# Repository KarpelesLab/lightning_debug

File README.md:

# Lightning debug board

A carrier board for an eLabGuy Lightning **male** breakout, for poking at (early)
iPhones from Linux. Plug a phone into the breakout and you get:

- **An FPGA on every Lightning signal pin.** All 12 data/ID contacts (both sides
  of the plug) go to an iCE40UP5K. It can sniff, emulate an accessory/cable chip
  (ID0/ID1), or drive a UART on the data lanes and stream it to the host.
- **USB-C #1 (DEBUG)** to the host. An FT2232H programs the FPGA's flash
  (`iceprog`) and gives a second channel (UART up to 12 Mbaud, or 30 MHz MPSSE)
  for log streaming. This port also powers the board.
- **USB-C #2 (PHONE)** for the phone's own USB. Analog switches connect the
  phone's USB lane straight through to a second host at full 480 Mb/s, or hand
  the lane to the FPGA instead. The FPGA also switches the phone's power (VBUS
  from this port, current-limited to 1 A).

KiCad 10 project: `lightning_debug.kicad_pro`. Board status: **routed, DRC
clean, fab files in `fab/release/`** (see [Status](#status) for what to check
before ordering).

| Top | Bottom |
|-----|--------|
|  |  |

*KiCad's stock libraries have no 3D models for the HRO USB-C receptacles or the
ASE oscillator, so those show only their pads. The breakout itself (J3/J4) is
drawn as its outline.*

## Architecture

```
 USB-C #1 (debug) ──► FT2232H ──ch.A (MPSSE/SPI)──► W25Q128 flash + iCE40 CRESET/CDONE   (iceprog)
       │                  └────ch.B (UART/MPSSE)──► iCE40UP5K bank 1
       └─ 5V ─► AP2112K 3.3 / 1.2 / 1.8

 USB-C #2 (phone) ─D+/D-─► FSUSB42 mux A ─► Lightning side A L0
                       └─► FSUSB42 mux B ─► Lightning side B L0
                                │ (other mux port = FPGA)
                VBUS2 ─► TPS2065C (FPGA PWR_EN, 1A) ─► Lightning PWR (pins 5/12)

 iCE40 bank 0 (VCCIO0, JP2: 3.3V default / 1.8V): L0 A/B (via the muxes), L1 A/B, EXP0-3, EXP5
 iCE40 bank 2 (1.8V):                             ID0/ID1 A/B, button, PWR fault, VBUS2 detect, EXP6
 iCE40 bank 1 (3.3V):                             SPI flash, 12 MHz clock, FT2232H ch.B, mux/power control
```

- **Both sides of the plug go to the FPGA,** so gateware handles orientation.
  GND (pins 1/16) and PWR (pins 5/12) are hard-wired.
- **Lightning pin map** (same on both breakouts):
  - Side A: 1 GND, 2 L0p, 3 L0n, 4 ID0, 5 PWR, 6 L1n, 7 L1p, 8 ID1.
  - Side B is mirrored: pin 17‑k carries the same signal as pin k (16 GND, 15 L0p, 14 L0n, 13 ID0, 12 PWR, 11 L1n, 10 L1p, 9 ID1).
- **Logic levels.** ID0/ID1 are 1.8 V (bank 2). The lanes' level isn't
  documented, so bank 0 is jumper-selectable: 3.3 V by default, 1.8 V via JP2.
- **USB passthrough** goes through analog muxes, not the FPGA, so it keeps
  480 Mb/s. Each mux works like this:

  | OE#  | SEL | Lightning L0 connected to |
  |------|-----|---------------------------|
  | 1    | x   | nothing (power-up default: 10k pull-up) |
  | 0    | 0   | FPGA (HSD1, rated for UART/USB) |
  | 0    | 1   | USB-C #2 (HSD2, USB only) |

  Enable at most one mux toward USB-C #2 at a time: the side the phone is touching.
- **Phone power** comes from USB-C #2 VBUS through the load switch. It is off
  by default (100k pull-down on PWR_EN). Bridge JP1 on 2‑3 instead of 1‑2 to
  power the phone from port 1.
- **33 Ω series resistors** sit on every FPGA ↔ Lightning line. Pull-ups on the
  ID lines are footprinted but not fitted.
- **User I/O:** button SW1, RGB LED (FPGA's constant-current sinks, `SB_RGBA_DRV`),
  and the 10-pin header J5. J5 pinout: 1 GND, 2 VCCIO0, 3–6 EXP0–3, 7 GND,
  8 EXP5, 9 EXP6, 10 +1V8. EXP4 was dropped: FPGA pin 42 could not be routed out
  past its neighbours, so it is left unconnected and J5 pin 7 is an extra GND.

### Solder jumpers

| JP  | default (1-2) | 2-3 |
|-----|---------------|-----|
| JP1 | phone PWR from USB-C #2 VBUS | from USB-C #1 (+5V) |
| JP2 | bank 0 (lanes) at 3.3V | bank 0 at 1.8V |

## Breakout install points (fit only ONE)

The two eLabGuy breakouts have mirrored pinouts, so each has its own footprint:

- **J3: APPLE-LM-BO-V1AV** (vertical plug). Top row is pins 1→8, bottom row 9→16.
- **J4: APPLE-LM-BO-V2A** (horizontal plug). Top row is 9→16, bottom row is
  8→1 with pin 1 at the bottom right. The plug hangs 10.7 mm past the board's
  left edge.

The footprints come from the drawings in `docs/` and are seen from the top,
with the breakout's silkscreen readable. **Before ordering, check one against a
real breakout:** print the PCB 1:1 and confirm the pin‑1 square pad position
and the plug direction. Both footprints have M3/M2 NPTH holes that line up with
the breakouts' own holes, for standoffs.

## Software

- Program the flash: `iceprog top.bin` (FT2232H default VID/PID 0403:6010; the
  EEPROM is optional).
- Logs: channel B shows up as `/dev/ttyUSB1`. UART runs up to 12 Mbaud, with
  RTS/CTS on BDBUS2/3. For more bandwidth, put channel B in MPSSE mode (SPI-like,
  30 MHz) on the same 4 pins.
- Pin constraints for nextpnr: `gateware/lightning_debug.pcf`.
- **Bring-up gateware:** `gateware/selftest.v` (`make -C gateware`, then
  `make -C gateware prog`). It uses every pin in the `.pcf`:
  - RGB LED cycles R → G → B.
  - J5 EXP pins output a slow binary count, so each header pin can be checked.
  - `/dev/ttyUSB1` at 115200 8N1 is a console. Any key prints a status line
    (ID lines, L1 and L0 lanes, button, VBUS2, power fault, power and mux
    state). `p` toggles Lightning power, `a`/`b` cycle mux A/B through
    off → FPGA → USB-C #2.
  - Holding the button forces Lightning power off.
  It builds with yosys + nextpnr-ice40 (or the pip-installable YoWASP builds, see
  the Makefile): no warnings, 233 LCs, 47 MHz achieved against the 12 MHz clock.

## PCB

- 80 × 50 mm, 4 layers, 1.6 mm:
  - **F.Cu:** signals.
  - **In1:** solid GND plane, the reference for the USB pairs. Only two short low-speed runs (EXP6, L1A_N_F) use it, kept 1 mm away from the USB nets.
  - **In2:** +3V3 pour plus signals; a lower-priority GND pour fills what the +3V3 pour can't reach.
  - **B.Cu:** signals plus GND pour.
- **Rules:** 0.15 mm track, 0.127 mm (5 mil) clearance, 0.5/0.3 mm vias. Power
  nets use 0.5 mm tracks and the USB/L0 nets 0.28 mm. All of this is inside
  JLCPCB's and PCBWay's standard 4-layer process.
- **Thermal and GND vias:** GND vias in the FPGA and FT2232H thermal pads, and
  GND stitching vias across the board.

## Status

- [x] Schematic: ERC clean (0 errors, 0 warnings).
- [x] PCB: placed, routed, DRC clean. That means 0 errors, 0 unconnected, and
      the board matches the schematic. The 4 remaining warnings come from the
      stock USB-C footprints' own silkscreen touching the board edge.
- [x] Gateware: `gateware/selftest.v` places and routes against the `.pcf`
      with every pin used, which confirms the pin file fits the SG48 package
      (banks, global clock input, RGB driver pins).
- [x] Netlist checked pin by pin against the datasheets:
  - **iCE40UP5K:** CRESET_B and CDONE have 10 kΩ pull-ups to SPI_VCCIO1 (3.3 V), as the datasheet asks.
  - **Config flash:** SPI_SO (pin 14) → flash DI, and SPI_SI (pin 17) ← flash DO.
  - **iceprog wiring:** the FT2232H port A pins match what iceprog expects: ADBUS0 SCK, ADBUS1 MOSI, ADBUS2 MISO, ADBUS4 CS, ADBUS6 CDONE, ADBUS7 CRESET.
  - **Pin banks:** IOB pins numbered 9 or lower are in bank 2 (1.8 V): button, power fault, VBUS2 detect, ID lines and EXP6. PWR_EN is on IOB_13b, which is bank 1 (3.3 V), and the TPS2065C's EN threshold is up to 2.0 V.
  - **FT2232H:** internal 1.8 V regulator wired to VCORE; VPHY/VPLL filtered through a ferrite; 12 kΩ 1 % REF resistor; TEST tied to GND; 93LC56B EEPROM with the 2.2 kΩ DO resistor.
  - **FSUSB42 (MSOP-10):** pinout matches the onsemi datasheet. SEL/OE are driven at 3.3 V (VIH 1.3 V). The defaults are OE high (disconnected) and SEL low (FPGA).
  - **Regulators, switch, ESD:** AP2112K, TPS2065C (DBV) and USBLC6-2SC6 pinouts match. USB-C CC pins have 5.1 kΩ to GND on both ports.
  - **VCCPLL:** the 100 Ω + 10 µF + 100 nF RC filter is the recommended "RC-based noise filter" (TN1252).
  - **RGB sinks:** the pins are rated 0–3.5 V regardless of VCCIO, so 3.3 V LED anodes are fine.
  - **VPP_2V5:** on 3.3 V, which master SPI configuration needs (≥ 2.3 V).
- [ ] **Signal integrity of the phone USB passthrough.** The USB2 D± and L0
      lanes (USB-C #2 → USBLC6 → FSUSB42 → breakout) were autorouted as
      separate 0.28 mm tracks, not coupled 90 Ω pairs.
      - The F.Cu parts sit over the solid In1 GND plane.
      - The parts on In2/B.Cu, about 30 mm per lane on the J3↔J4 legs and
        the mux → FPGA runs, often have no plane on the adjacent layer, because
        those two signal layers face each other across 0.2 mm. There the
        impedance is well above 90 Ω.
      - `tools/pour_islands.py` already rescues what pour it can with GND vias.
      - The two install points also leave a ~25 mm open stub on each lane from
        the unused connector.
      - FT2232H USB (USB-C #1) is short and fully referenced.
      - Expect full-speed and probably high-speed to work, but if the phone link
        has to be robust at 480 Mb/s, hand-route those lanes as coupled pairs
        on F.Cu or over a reserved GND area.
- [ ] Verify one breakout footprint 1:1 against the real part (see above).
- [x] LCSC part numbers: every BOM line has one, checked against the JLCPCB
      parts library (exact MPN, in stock) on 2026-11-09.

## Ordering (JLCPCB / PCBWay)

```
python3 tools/export_fab.py            # refuses while the board has unrouted nets / DRC errors
python3 tools/export_fab.py --preview  # dry run -> fab/UNROUTED-PREVIEW/ (DO NOT ORDER)
```

The script runs DRC first, then writes `fab/release/` (committed in this repo):

| File | JLCPCB | PCBWay |
|------|--------|--------|
| `lightning_debug-gerbers.zip` | "Add gerber file" | "Quick-order PCB" upload |
| `jlcpcb/bom.csv`, `jlcpcb/cpl.csv` | Assembly → BOM / CPL | – |
| `pcbway/bom.csv`, `pcbway/centroid.csv` | – | Assembly → BOM / Centroid |
| `assembly-excluded.txt` | parts you fit yourself (breakout, J5 header, DNP) | same |

PCB options to select:
- 4 layers, 1.6 mm thick, 80 × 50 mm, FR-4, 1 oz outer copper.
- Min track/space 0.15/0.127 mm, min via 0.3/0.5 mm.
- Impedance control on, for the USB pairs. Choose the fab's stackup (for
  JLCPCB, e.g. JLC04161H-7628).
- Assembly on the top side only. Every SMD part is on top.

Before you pay:
- **Part numbers.** `tools/parts.csv` has an LCSC number (JLCPCB) and
  manufacturer/MPN (PCBWay) for every BOM line. All were checked against
  the JLCPCB library on 2026-11-09: exact MPN match, in stock.
  - The resistors, most capacitors, the ferrite, the 12 MHz crystal, the red
    LED and the flash are JLCPCB basic parts. The rest are extended parts,
    which carry a per-part setup fee.
  - Watch the stock on the FT2232HQ (C193662, about 55 at the time) and the
    iCE40UP5K. The iCE40 is the tray variant ICE40UP5K-SG48I (C2678152), the
    same chip as the -SG48ITR reel part named in the schematic.
  - The status LEDs are the KENTO KT-0603 series, because the usual Everlight
    0603 LEDs were out of stock.
- **Rotation.** Check part rotation in the fab's placement preview, especially
  for the QFNs, SOT-23s, SOICs and USB-C connectors. KiCad's zero orientation
  and JLCPCB/PCBWay's don't always agree, and both let you fix it in their viewer.
- **Origin.** CPL coordinates use the board's bottom-left corner as origin
  (drill/place origin), with Y pointing up.

## Regenerating

The KiCad files were bootstrapped by the scripts in `tools/`. You can edit the
schematic and PCB in KiCad directly. To redo everything from the scripts:

```
python3 tools/gen_symlib.py && python3 tools/gen_footprints.py
python3 tools/gen_schematic.py && kicad-cli sch upgrade lightning_debug.kicad_sch
kicad-cli sch export netlist --format kicadxml -o /tmp/net.xml lightning_debug.kicad_sch
python3 tools/gen_pcb.py /tmp/net.xml        # WARNING: overwrites the PCB (placement, no tracks)
python3 tools/autoroute.py                   # Freerouting, headless
python3 tools/finish_route.py                # rip-up/re-route what is left, GND stitching
python3 tools/pour_islands.py                # In2 GND fill + GND vias so pour islands survive
python3 tools/silk.py                        # place reference designators
```

- `autoroute.py` runs [Freerouting](https://github.com/freerouting/freerouting) 2.x
  **headless** (`--gui.enabled=false`, no `DISPLAY`, `java.awt.headless`). It uses
  the newest `~/.local/share/freerouting/freerouting-2.*.jar` and a Java 25
  runtime for 2.5+ (or set `FREEROUTING_JAR` / `FREEROUTING_JAVA`).
- `finish_route.py` is a small grid A* router built on KiCad's own geometry. It:
  - takes the autorouter's open connections from KiCad's DRC report;
  - keeps In1 free of tracks, except as a last resort for low-speed nets, 1 mm from the USB nets;
  - rips up neighbours only when plain routing makes no progress.
- The autorouter results depend on placement. The committed board comes from
  several placement variants (`PCB_U7`/`PCB_MARGIN` knobs in `gen_pcb.py`). The
  one routed and committed had the FPGA rotated 90°. Even then, the last
  connection (EXP4) was dropped by hand, so a fresh run won't necessarily come
  out clean.

Refresh the 3D renders:

```
kicad-cli pcb render -o renders/top.png --side top --quality high --background opaque -w 1600 -h 1000 --zoom 1.1 lightning_debug.kicad_pcb
kicad-cli pcb render -o renders/bottom.png --side bottom --quality high --background opaque -w 1600 -h 1000 --zoom 1.1 lightning_debug.kicad_pcb
kicad-cli pcb render -o renders/iso.png --quality high --background opaque --perspective --rotate '-50,0,-30' -w 1600 -h 1000 --zoom 0.9 lightning_debug.kicad_pcb
```

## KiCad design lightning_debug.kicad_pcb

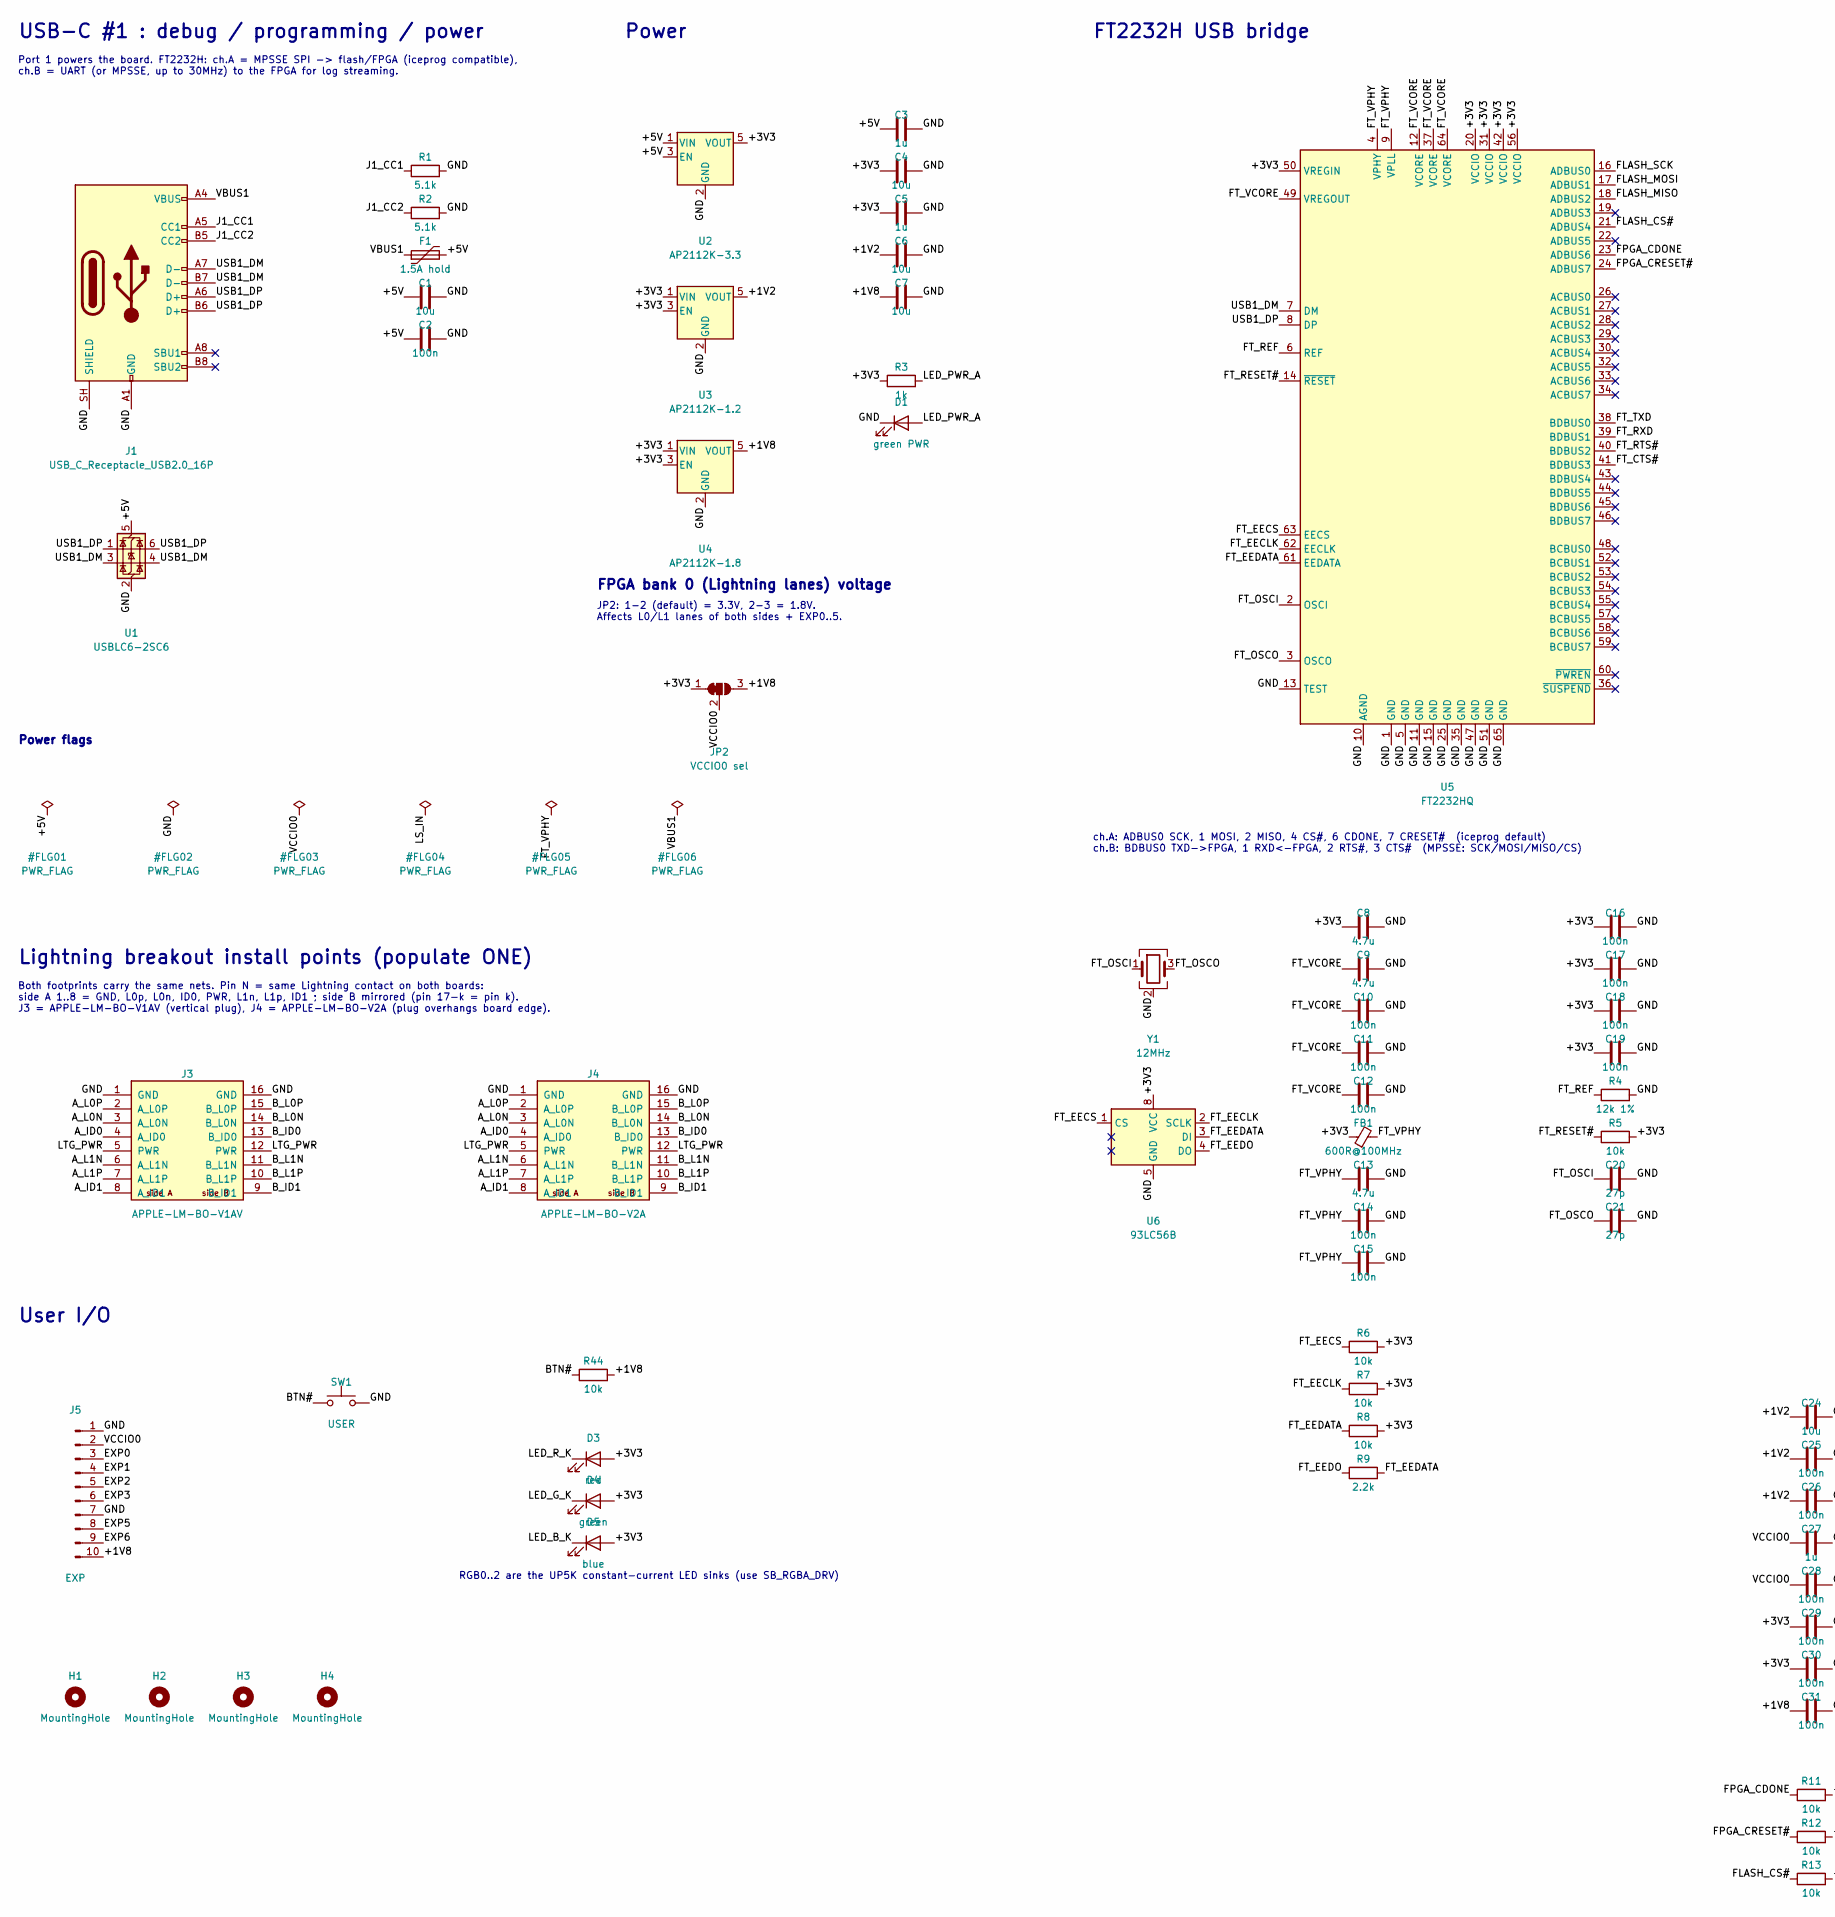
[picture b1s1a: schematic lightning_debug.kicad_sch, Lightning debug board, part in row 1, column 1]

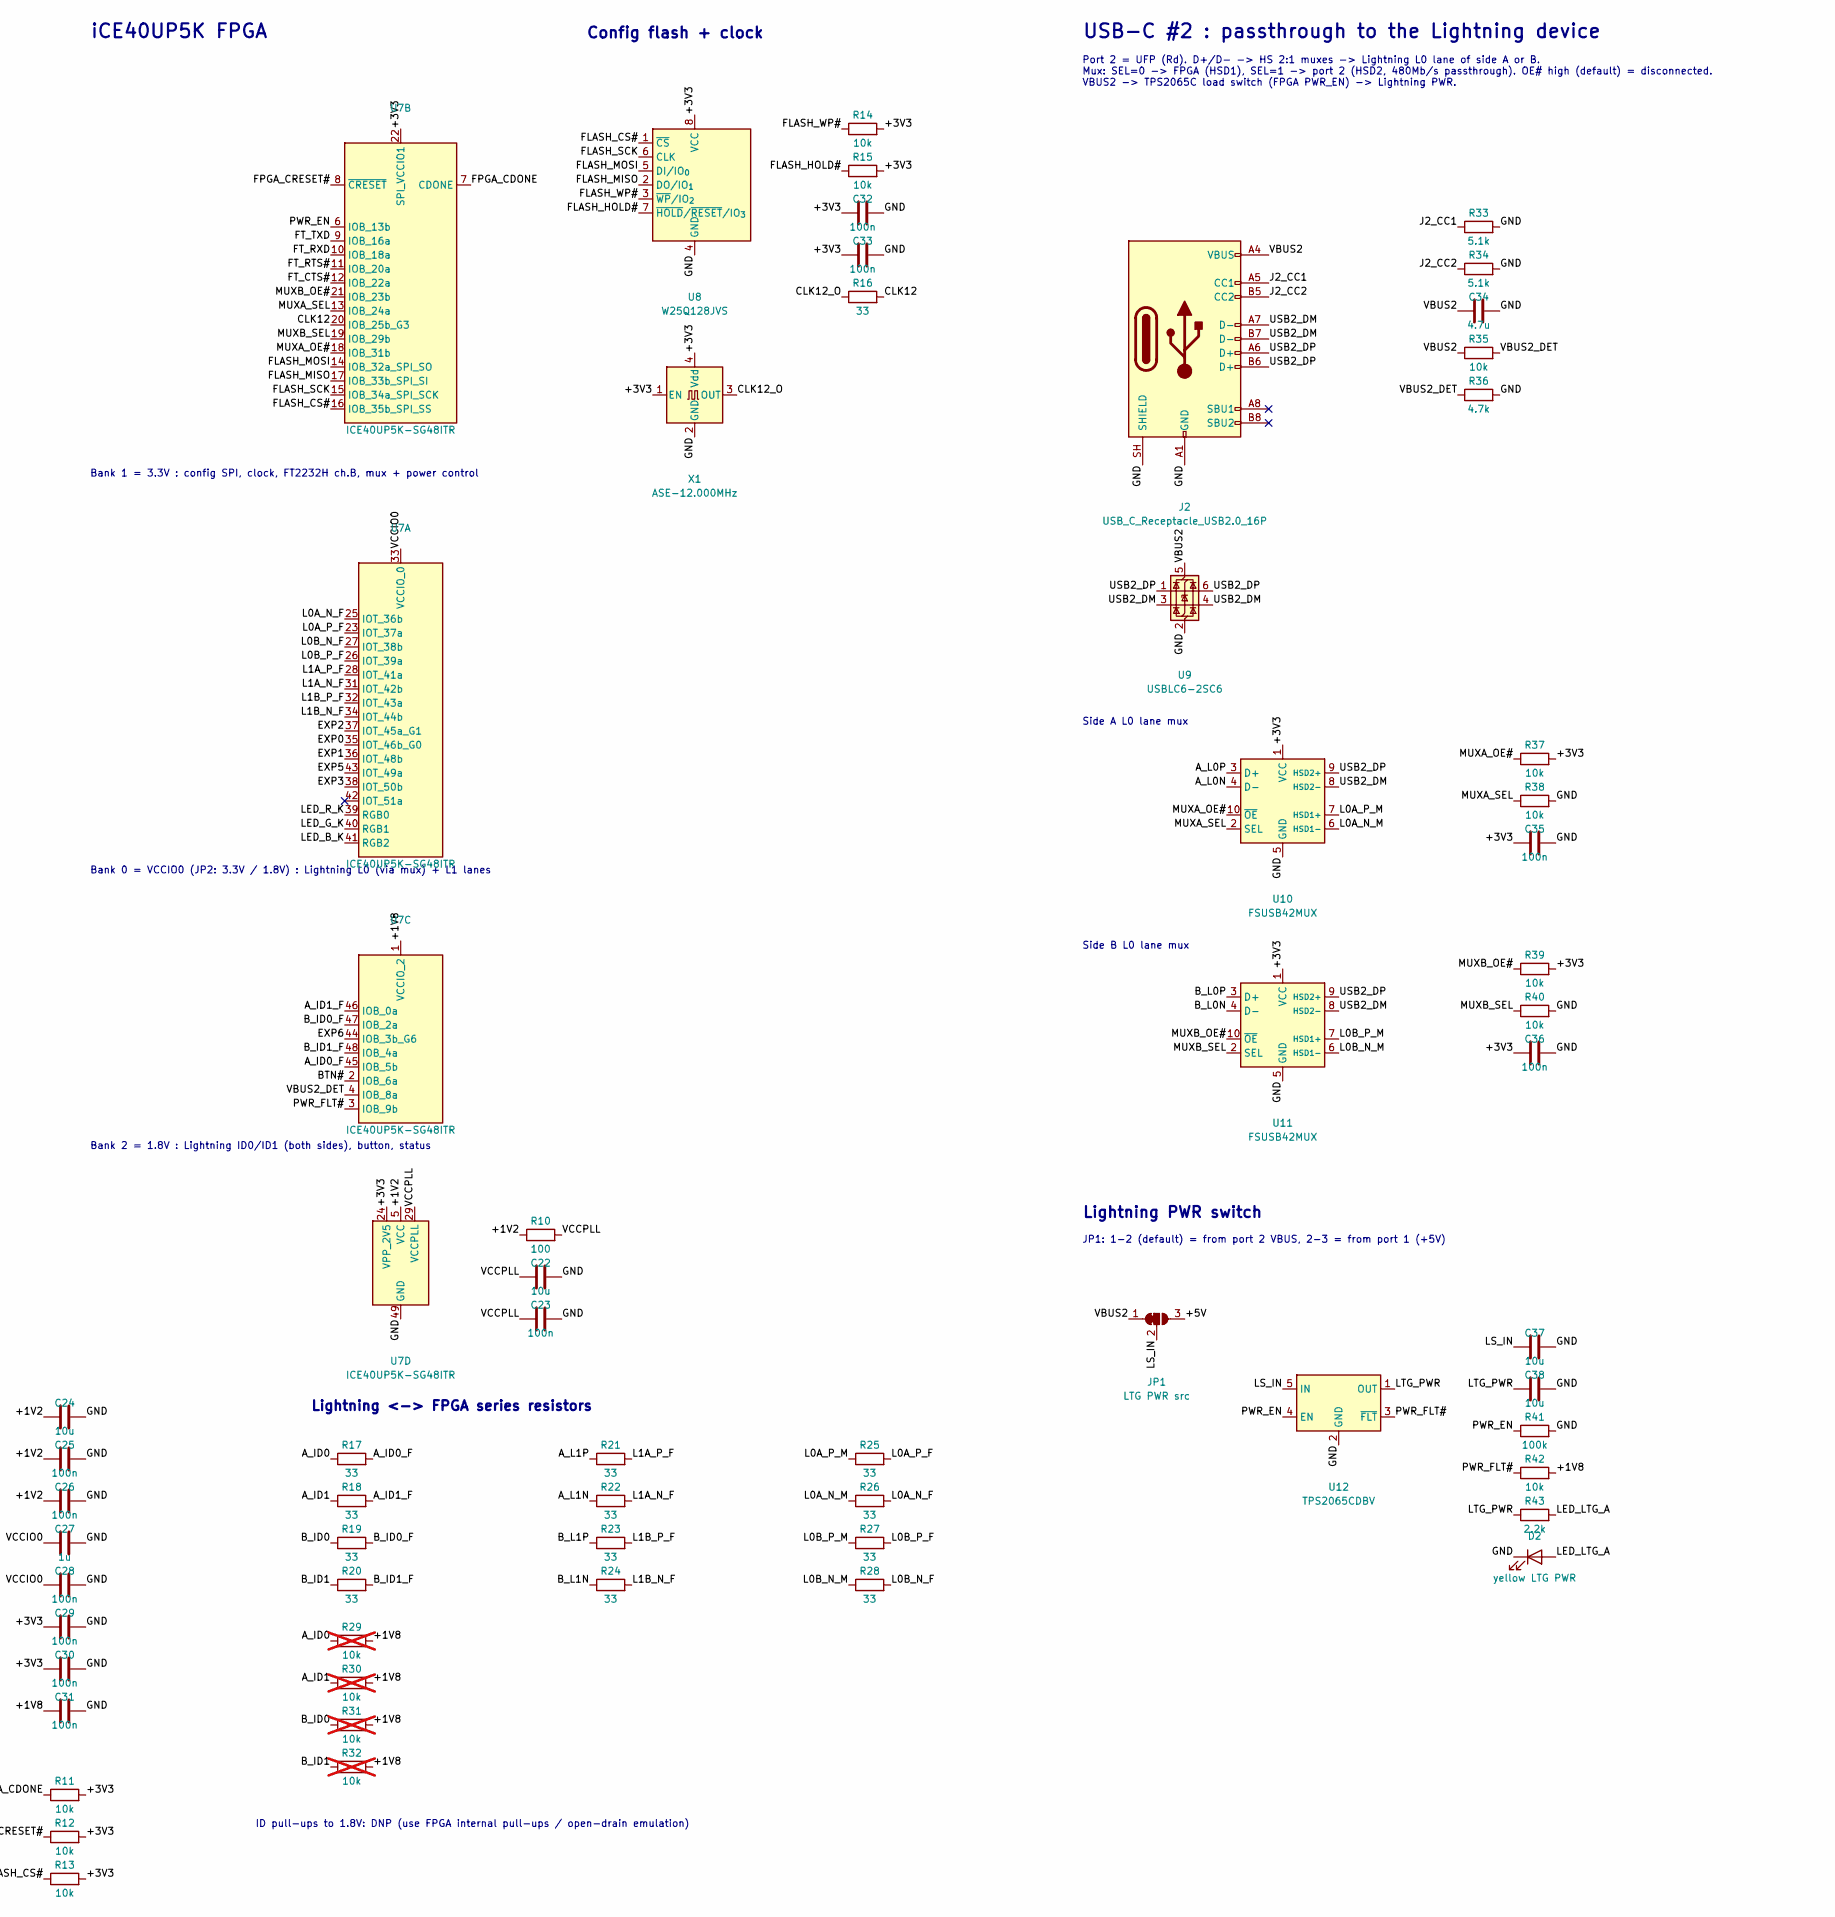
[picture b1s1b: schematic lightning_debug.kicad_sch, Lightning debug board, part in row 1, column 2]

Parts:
C1, C4, C6, C7, C22, C24, C37, C38: 10u; C_0805_2012Metric
C2, C10, C11, C12, C14, C15, C16, C17, C18, C19, C23, C25, C26, C28, C29, C30, C31, C32, C33, C35, C36: 100n; C_0603_1608Metric
C3, C5, C27: 1u; C_0603_1608Metric
C8, C9, C13, C34: 4.7u; C_0805_2012Metric
C20, C21: 27p; C_0603_1608Metric
D1: green PWR; LED_0603_1608Metric
D2: yellow LTG PWR; LED_0603_1608Metric
D3: red; LED_0603_1608Metric
D4: green; LED_0603_1608Metric
D5: blue; LED_0603_1608Metric
F1: 1.5A hold; Fuse_1206_3216Metric
FB1: 600R@100MHz; L_0603_1608Metric
H1, H2, H3, H4: MountingHole; MountingHole_3.2mm_M3
J1, J2: USB_C_Receptacle_USB2.0_16P; USB_C_Receptacle_HRO_TYPE-C-31-M-12
J3: APPLE-LM-BO-V1AV; eLabGuy_APPLE-LM-BO-V1AV
J4: APPLE-LM-BO-V2A; eLabGuy_APPLE-LM-BO-V2A
J5: EXP; PinHeader_1x10_P2.54mm_Vertical
JP1: LTG PWR src; SolderJumper-3_P1.3mm_Bridged12_RoundedPad1.0x1.5mm
JP2: VCCIO0 sel; SolderJumper-3_P1.3mm_Bridged12_RoundedPad1.0x1.5mm
R1, R2, R33, R34: 5.1k; R_0603_1608Metric
R3: 1k; R_0603_1608Metric
R4: 12k 1%; R_0603_1608Metric
R5, R6, R7, R8, R11, R12, R13, R14, R15, R35, R37, R38, R39, R40, R42, R44: 10k; R_0603_1608Metric
R9, R43: 2.2k; R_0603_1608Metric
R10: 100; R_0603_1608Metric
R16, R17, R18, R19, R20, R21, R22, R23, R24, R25, R26, R27, R28: 33; R_0603_1608Metric
R29, R30, R31, R32: 10k; R_0603_1608Metric; not fitted
R36: 4.7k; R_0603_1608Metric
R41: 100k; R_0603_1608Metric
SW1: USER; SW_SPST_PTS810
U1, U9: USBLC6-2SC6; SOT-23-6
U2: AP2112K-3.3; SOT-23-5
U3: AP2112K-1.2; SOT-23-5
U4: AP2112K-1.8; SOT-23-5
U5: FT2232HQ; QFN-64-1EP_9x9mm_P0.5mm_EP4.35x4.35mm
U6: 93LC56B; SOIC-8_3.9x4.9mm_P1.27mm
U7: ICE40UP5K-SG48ITR; QFN-48-1EP_7x7mm_P0.5mm_EP5.6x5.6mm
U8: W25Q128JVS; SOIC-8_5.3x5.3mm_P1.27mm
U10, U11: FSUSB42MUX; MSOP-10_3x3mm_P0.5mm
U12: TPS2065CDBV; SOT-23-5
X1: ASE-12.000MHz; Oscillator_SMD_Abracon_ASE-4Pin_3.2x2.5mm
Y1: 12MHz; Crystal_SMD_3225-4Pin_3.2x2.5mm

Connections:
/+1V2: C6.1, C24.1, C25.1, C26.1, R10.1, U3.5 (VOUT), U7.5 (VCC), U7.30 (VCC)
/+1V8: C7.1, C31.1, J5.10, JP2.3 (B), R29.2, R30.2, R31.2, R32.2, R42.2, R44.2, U4.5 (VOUT), U7.1 (VCCIO_2)
/+3V3: C4.1, C5.1, C8.1, C16.1, C17.1, C18.1, C19.1, C29.1, C30.1, C32.1, C33.1, C35.1, C36.1, D3.2 (A), D4.2 (A), D5.2 (A), FB1.1, JP2.1 (A), R3.1, R5.2, R6.2, R7.2, R8.2, R11.2, R12.2, R13.2, R14.2, R15.2, R37.2, R39.2, U2.5 (VOUT), U3.1 (VIN), U3.3 (EN), U4.1 (VIN), U4.3 (EN), U5.20 (VCCIO), U5.31 (VCCIO), U5.42 (VCCIO), U5.50 (VREGIN), U5.56 (VCCIO), U6.8 (VCC), U7.22 (SPI_VCCIO1), U7.24 (VPP_2V5), U8.8 (VCC), U10.1 (VCC), U11.1 (VCC), X1.1 (EN), X1.4 (Vdd)
/+5V: C1.1, C2.1, C3.1, F1.2, JP1.3 (B), U1.5 (VBUS), U2.1 (VIN), U2.3 (EN)
/A_ID0: J3.4 (A_ID0), J4.4 (A_ID0), R17.1, R29.1
/A_ID0_F: R17.2, U7.45 (IOB_5b)
/A_ID1: J3.8 (A_ID1), J4.8 (A_ID1), R18.1, R30.1
/A_ID1_F: R18.2, U7.46 (IOB_0a)
/A_L0N: J3.3 (A_L0N), J4.3 (A_L0N), U10.4 (D-)
/A_L0P: J3.2 (A_L0P), J4.2 (A_L0P), U10.3 (D+)
/A_L1N: J3.6 (A_L1N), J4.6 (A_L1N), R22.1
/A_L1P: J3.7 (A_L1P), J4.7 (A_L1P), R21.1
/BTN#: R44.1, SW1.1, U7.2 (IOB_6a)
/B_ID0: J3.13 (B_ID0), J4.13 (B_ID0), R19.1, R31.1
/B_ID0_F: R19.2, U7.47 (IOB_2a)
/B_ID1: J3.9 (B_ID1), J4.9 (B_ID1), R20.1, R32.1
/B_ID1_F: R20.2, U7.48 (IOB_4a)
/B_L0N: J3.14 (B_L0N), J4.14 (B_L0N), U11.4 (D-)
/B_L0P: J3.15 (B_L0P), J4.15 (B_L0P), U11.3 (D+)
/B_L1N: J3.11 (B_L1N), J4.11 (B_L1N), R24.1
/B_L1P: J3.10 (B_L1P), J4.10 (B_L1P), R23.1
/CLK12: R16.2, U7.20 (IOB_25b_G3)
/CLK12_O: R16.1, X1.3 (OUT)
/EXP0: J5.3, U7.35 (IOT_46b_G0)
/EXP1: J5.4, U7.36 (IOT_48b)
/EXP2: J5.5, U7.37 (IOT_45a_G1)
/EXP3: J5.6, U7.38 (IOT_50b)
/EXP5: J5.8, U7.43 (IOT_49a)
/EXP6: J5.9, U7.44 (IOB_3b_G6)
/FLASH_CS#: R13.1, U5.21 (ADBUS4), U7.16 (IOB_35b_SPI_SS), U8.1 (~CS)
/FLASH_HOLD#: R15.1, U8.7 (~HOLD/~RESET/IO_{3})
/FLASH_MISO: U5.18 (ADBUS2), U7.17 (IOB_33b_SPI_SI), U8.2 (DO/IO_{1})
/FLASH_MOSI: U5.17 (ADBUS1), U7.14 (IOB_32a_SPI_SO), U8.5 (DI/IO_{0})
/FLASH_SCK: U5.16 (ADBUS0), U7.15 (IOB_34a_SPI_SCK), U8.6 (CLK)
/FLASH_WP#: R14.1, U8.3 (~WP/IO_{2})
/FPGA_CDONE: R11.1, U5.23 (ADBUS6), U7.7 (CDONE)
/FPGA_CRESET#: R12.1, U5.24 (ADBUS7), U7.8 (~CRESET)
/FT_CTS#: U5.41 (BDBUS3), U7.12 (IOB_22a)
/FT_EECLK: R7.1, U5.62 (EECLK), U6.2 (SCLK)
/FT_EECS: R6.1, U5.63 (EECS), U6.1 (CS)
/FT_EEDATA: R8.1, R9.2, U5.61 (EEDATA), U6.3 (DI)
/FT_EEDO: R9.1, U6.4 (DO)
/FT_OSCI: C20.1, U5.2 (OSCI), Y1.1
/FT_OSCO: C21.1, U5.3 (OSCO), Y1.3
/FT_REF: R4.1, U5.6 (REF)
/FT_RESET#: R5.1, U5.14 (~RESET)
/FT_RTS#: U5.40 (BDBUS2), U7.11 (IOB_20a)
/FT_RXD: U5.39 (BDBUS1), U7.10 (IOB_18a)
/FT_TXD: U5.38 (BDBUS0), U7.9 (IOB_16a)
/FT_VCORE: C9.1, C10.1, C11.1, C12.1, U5.12 (VCORE), U5.37 (VCORE), U5.49 (VREGOUT), U5.64 (VCORE)
/FT_VPHY: C13.1, C14.1, C15.1, FB1.2, U5.4 (VPHY), U5.9 (VPLL)
/GND: C1.2, C2.2, C3.2, C4.2, C5.2, C6.2, C7.2, C8.2, C9.2, C10.2, C11.2, C12.2, C13.2, C14.2, C15.2, C16.2, C17.2, C18.2, C19.2, C20.2, C21.2, C22.2, C23.2, C24.2, C25.2, C26.2, C27.2, C28.2, C29.2, C30.2, C31.2, C32.2, C33.2, C34.2, C35.2, C36.2, C37.2, C38.2, D1.1 (K), D2.1 (K), J1.A1 (GND), J1.A12 (GND), J1.B1 (GND), J1.B12 (GND), J1.SH (SHIELD), J2.A1 (GND), J2.A12 (GND), J2.B1 (GND), J2.B12 (GND), J2.SH (SHIELD), J3.1 (GND), J3.16 (GND), J4.1 (GND), J4.16 (GND), J5.1, J5.7, R1.2, R2.2, R4.2, R33.2, R34.2, R36.2, R38.2, R40.2, R41.2, SW1.2, U1.2 (GND), U2.2 (GND), U3.2 (GND), U4.2 (GND), U5.1 (GND), U5.5 (GND), U5.10 (AGND), U5.11 (GND), U5.13 (TEST), U5.15 (GND), U5.25 (GND), U5.35 (GND), U5.47 (GND), U5.51 (GND), U5.65 (GND), U6.5 (GND), U7.49 (GND), U8.4 (GND), U9.2 (GND), U10.5 (GND), U11.5 (GND), U12.2 (GND), X1.2 (GND), Y1.2 (G), Y1.4 (G)
/J1_CC1: J1.A5 (CC1), R1.1
/J1_CC2: J1.B5 (CC2), R2.1
/J2_CC1: J2.A5 (CC1), R33.1
/J2_CC2: J2.B5 (CC2), R34.1
/L0A_N_F: R26.2, U7.25 (IOT_36b)
/L0A_N_M: R26.1, U10.6 (HSD1-)
/L0A_P_F: R25.2, U7.23 (IOT_37a)
/L0A_P_M: R25.1, U10.7 (HSD1+)
/L0B_N_F: R28.2, U7.27 (IOT_38b)
/L0B_N_M: R28.1, U11.6 (HSD1-)
/L0B_P_F: R27.2, U7.26 (IOT_39a)
/L0B_P_M: R27.1, U11.7 (HSD1+)
/L1A_N_F: R22.2, U7.31 (IOT_42b)
/L1A_P_F: R21.2, U7.28 (IOT_41a)
/L1B_N_F: R24.2, U7.34 (IOT_44b)
/L1B_P_F: R23.2, U7.32 (IOT_43a)
/LED_B_K: D5.1 (K), U7.41 (RGB2)
/LED_G_K: D4.1 (K), U7.40 (RGB1)
/LED_LTG_A: D2.2 (A), R43.2
/LED_PWR_A: D1.2 (A), R3.2
/LED_R_K: D3.1 (K), U7.39 (RGB0)
/LS_IN: C37.1, JP1.2 (C), U12.5 (IN)
/LTG_PWR: C38.1, J3.5 (PWR), J3.12 (PWR), J4.5 (PWR), J4.12 (PWR), R43.1, U12.1 (OUT)
/MUXA_OE#: R37.1, U7.18 (IOB_31b), U10.10 (~OE)
/MUXA_SEL: R38.1, U7.13 (IOB_24a), U10.2 (SEL)
/MUXB_OE#: R39.1, U7.21 (IOB_23b), U11.10 (~OE)
/MUXB_SEL: R40.1, U7.19 (IOB_29b), U11.2 (SEL)
/PWR_EN: R41.1, U7.6 (IOB_13b), U12.4 (EN)
/PWR_FLT#: R42.1, U7.3 (IOB_9b), U12.3 (~FLT)
/USB1_DM: J1.A7 (D-), J1.B7 (D-), U1.3 (I/O2), U1.4 (I/O2), U5.7 (DM)
/USB1_DP: J1.A6 (D+), J1.B6 (D+), U1.1 (I/O1), U1.6 (I/O1), U5.8 (DP)
/USB2_DM: J2.A7 (D-), J2.B7 (D-), U9.3 (I/O2), U9.4 (I/O2), U10.8 (HSD2-), U11.8 (HSD2-)
/USB2_DP: J2.A6 (D+), J2.B6 (D+), U9.1 (I/O1), U9.6 (I/O1), U10.9 (HSD2+), U11.9 (HSD2+)
/VBUS1: F1.1, J1.A4 (VBUS), J1.A9 (VBUS), J1.B4 (VBUS), J1.B9 (VBUS)
/VBUS2: C34.1, J2.A4 (VBUS), J2.A9 (VBUS), J2.B4 (VBUS), J2.B9 (VBUS), JP1.1 (A), R35.1, U9.5 (VBUS)
/VBUS2_DET: R35.2, R36.1, U7.4 (IOB_8a)
/VCCIO0: C27.1, C28.1, J5.2, JP2.2 (C), U7.33 (VCCIO_0)
/VCCPLL: C22.1, C23.1, R10.2, U7.29 (VCCPLL)

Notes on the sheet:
User I/O
ch.A: ADBUS0 SCK, 1 MOSI, 2 MISO, 4 CS#, 6 CDONE, 7 CRESET# (iceprog default) ch.B: BDBUS0 TXD->FPGA, 1 RXD<-FPGA, 2 RTS#, 3 CTS# (MPSSE: SCK/MOSI/MISO/CS)
Power flags
Lightning PWR switch
RGB0..2 are the UP5K constant-current LED sinks (use SB_RGBA_DRV)
JP2: 1-2 (default) = 3.3V, 2-3 = 1.8V. Affects L0/L1 lanes of both sides + EXP0..5.
FT2232H USB bridge
Port 2 = UFP (Rd). D+/D- -> HS 2:1 muxes -> Lightning L0 lane of side A or B. Mux: SEL=0 -> FPGA (HSD1), SEL=1 -> port 2 (HSD2, 480Mb/s passthrough). OE# high (default) = disconnected. VBUS2 -> TPS2065C load switch (FPGA PWR_EN) -> Lightning PWR.
Lightning <-> FPGA series resistors
iCE40UP5K FPGA
Bank 0 = VCCIO0 (JP2: 3.3V / 1.8V) : Lightning L0 (via mux) + L1 lanes
USB-C #2 : passthrough to the Lightning device
Port 1 powers the board. FT2232H: ch.A = MPSSE SPI -> flash/FPGA (iceprog compatible), ch.B = UART (or MPSSE, up to 30MHz) to the FPGA for log streaming.
Both footprints carry the same nets. Pin N = same Lightning contact on both boards: side A 1..8 = GND, L0p, L0n, ID0, PWR, L1n, L1p, ID1 ; side B mirrored (pin 17-k = pin k). J3 = APPLE-LM-BO-V1AV (vertical plug), J4 = APPLE-LM-BO-V2A (plug overhangs board edge).
FPGA bank 0 (Lightning lanes) voltage
USB-C #1 : debug / programming / power
Bank 2 = 1.8V : Lightning ID0/ID1 (both sides), button, status
Side B L0 lane mux
Lightning breakout install points (populate ONE)
Power
Config flash + clock
Bank 1 = 3.3V : config SPI, clock, FT2232H ch.B, mux + power control
Side A L0 lane mux
ID pull-ups to 1.8V: DNP (use FPGA internal pull-ups / open-drain emulation)
JP1: 1-2 (default) = from port 2 VBUS, 2-3 = from port 1 (+5V)

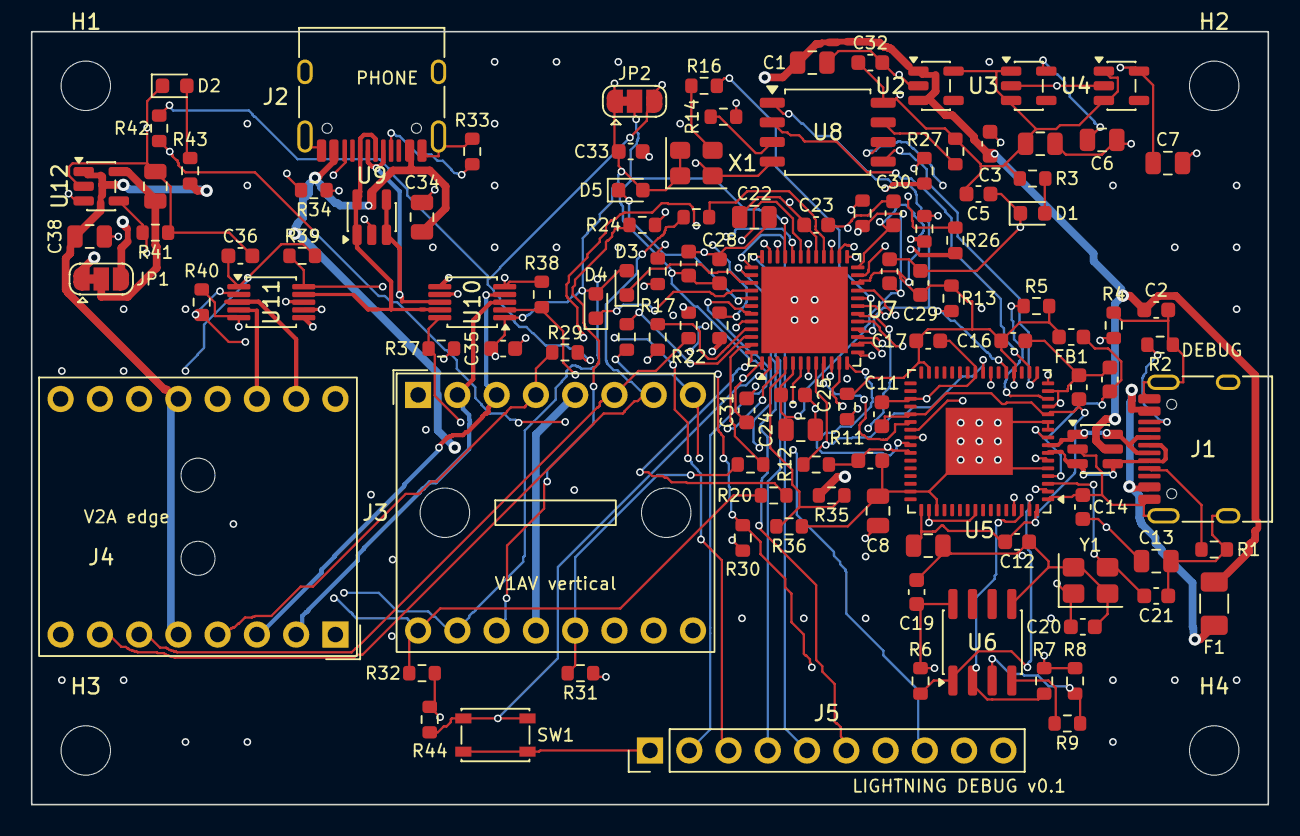
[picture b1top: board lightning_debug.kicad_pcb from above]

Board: 4 copper layers, 80.0 x 50.0 mm, 115 parts (0 on the bottom side), 90 nets.

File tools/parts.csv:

# Part numbers merged into the BOM by tools/export_fab.py (key = value + footprint).
# Fill lcsc for JLCPCB (search jlcpcb.com/parts); manufacturer/mpn for PCBWay.
# Only FSUSB42MUX LCSC was verified (C11355). Check MPN suffixes against stock.
value,footprint,lcsc,manufacturer,mpn,refs
USER,Button_Switch_SMD:SW_SPST_PTS810,,C&K,PTS810SJM250SMTRLFS,SW1
100n,Capacitor_SMD:C_0603_1608Metric,,,,C2 C10 C11 C12 C14 C15 C16 C17 C18 C19 C23 C25 C26 C28 C29 C30 C31 C32 C33 C35 C36
1u,Capacitor_SMD:C_0603_1608Metric,,,,C3 C5 C27
27p,Capacitor_SMD:C_0603_1608Metric,,,,C20 C21
10u,Capacitor_SMD:C_0805_2012Metric,,,,C1 C4 C6 C7 C22 C24 C37 C38
4.7u,Capacitor_SMD:C_0805_2012Metric,,,,C8 C9 C13 C34
USB_C_Receptacle_USB2.0_16P,Connector_USB:USB_C_Receptacle_HRO_TYPE-C-31-M-12,,Korean Hroparts,TYPE-C-31-M-12,J1 J2
12MHz,Crystal:Crystal_SMD_3225-4Pin_3.2x2.5mm,,,,Y1
1.5A hold,Fuse:Fuse_1206_3216Metric,,,,F1
600R@100MHz,Inductor_SMD:L_0603_1608Metric,,,,FB1
blue,LED_SMD:LED_0603_1608Metric,,,,D5
green,LED_SMD:LED_0603_1608Metric,,,,D4
green PWR,LED_SMD:LED_0603_1608Metric,,,,D1
red,LED_SMD:LED_0603_1608Metric,,,,D3
yellow LTG PWR,LED_SMD:LED_0603_1608Metric,,,,D2
ASE-12.000MHz,Oscillator:Oscillator_SMD_Abracon_ASE-4Pin_3.2x2.5mm,,Abracon,ASE-12.000MHZ-LC-T,X1
ICE40UP5K-SG48ITR,Package_DFN_QFN:QFN-48-1EP_7x7mm_P0.5mm_EP5.6x5.6mm,,Lattice,ICE40UP5K-SG48ITR,U7
FT2232HQ,Package_DFN_QFN:QFN-64-1EP_9x9mm_P0.5mm_EP4.35x4.35mm,,FTDI,FT2232HQ-REEL,U5
FSUSB42MUX,Package_SO:MSOP-10_3x3mm_P0.5mm,C11355,onsemi,FSUSB42MUX,U10 U11
93LC56B,Package_SO:SOIC-8_3.9x4.9mm_P1.27mm,,Microchip,93LC56BT-I/SN,U6
W25Q128JVS,Package_SO:SOIC-8_5.3x5.3mm_P1.27mm,,Winbond,W25Q128JVSIQ,U8
AP2112K-1.2,Package_TO_SOT_SMD:SOT-23-5,,Diodes Inc,AP2112K-1.2TRG1,U3
AP2112K-1.8,Package_TO_SOT_SMD:SOT-23-5,,Diodes Inc,AP2112K-1.8TRG1,U4
AP2112K-3.3,Package_TO_SOT_SMD:SOT-23-5,,Diodes Inc,AP2112K-3.3TRG1,U2
TPS2065CDBV,Package_TO_SOT_SMD:SOT-23-5,,Texas Instruments,TPS2065CDBVR,U12
USBLC6-2SC6,Package_TO_SOT_SMD:SOT-23-6,,STMicroelectronics,USBLC6-2SC6,U1 U9
100,Resistor_SMD:R_0603_1608Metric,,,,R10
100k,Resistor_SMD:R_0603_1608Metric,,,,R41
10k,Resistor_SMD:R_0603_1608Metric,,,,R5 R6 R7 R8 R11 R12 R13 R14 R15 R29 R30 R31 R32 R35 R37 R38 R39 R40 R42 R44
12k 1%,Resistor_SMD:R_0603_1608Metric,,,,R4
1k,Resistor_SMD:R_0603_1608Metric,,,,R3
2.2k,Resistor_SMD:R_0603_1608Metric,,,,R9 R43
33,Resistor_SMD:R_0603_1608Metric,,,,R16 R17 R18 R19 R20 R21 R22 R23 R24 R25 R26 R27 R28
4.7k,Resistor_SMD:R_0603_1608Metric,,,,R36
5.1k,Resistor_SMD:R_0603_1608Metric,,,,R1 R2 R33 R34

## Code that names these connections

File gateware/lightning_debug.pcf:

# iCE40UP5K-SG48 pin constraints for the Lightning debug board (nextpnr-ice40 --up5k --package sg48)
# Generated from tools/gen_schematic.py assignments - keep in sync.

# ---- clock (12 MHz oscillator X1, bank 1, global G3) ----
set_io clk12        20

# ---- FT2232H channel B (bank 1, 3.3V) : UART or MPSSE ----
set_io ft_txd       9    # FT -> FPGA (UART RX / MPSSE SCK)
set_io ft_rxd       10   # FPGA -> FT (UART TX)
set_io ft_rts_n     11   # FT -> FPGA
set_io ft_cts_n     12   # FPGA -> FT

# ---- config SPI flash (shared with FT2232H ch.A / iceprog) ----
set_io flash_mosi   14
set_io flash_sck    15
set_io flash_cs_n   16
set_io flash_miso   17

# ---- L0 lane muxes (FSUSB42): SEL=0 -> FPGA, SEL=1 -> USB-C #2; OE_n=1 -> disconnected ----
set_io muxa_sel     13
set_io muxa_oe_n    18
set_io muxb_sel     19
set_io muxb_oe_n    21

# ---- Lightning PWR load switch (TPS2065C, active high, 1A) ----
set_io pwr_en       6

# ---- Lightning lanes (bank 0, VCCIO0 = 3.3V default / 1.8V via JP2) ----
set_io l0a_p        23   # side A L0+ (through mux A HSD1)
set_io l0a_n        25
set_io l0b_p        26   # side B L0+ (through mux B HSD1)
set_io l0b_n        27
set_io l1a_p        28   # side A L1+ (direct, 33R)
set_io l1a_n        31
set_io l1b_p        32
set_io l1b_n        34

# ---- spare I/O on J5 ----
set_io exp0         35   # bank 0, G0
set_io exp1         36
set_io exp2         37   # bank 0, G1
set_io exp3         38
# exp4: FPGA pin 42 is not connected (it could not be routed out); J5 pin 7 is GND
set_io exp5         43
set_io exp6         44   # bank 2 (1.8V), G6

# ---- Lightning ID lines (bank 2, 1.8V) ----
set_io a_id0        45
set_io a_id1        46
set_io b_id0        47
set_io b_id1        48

# ---- misc (bank 2, 1.8V) ----
set_io btn_n        2    # user button, active low (10k pull-up)
set_io pwr_flt_n    3    # TPS2065C fault, open drain (10k pull-up to 1.8V)
set_io vbus2_det    4    # USB-C #2 VBUS present (10k/4.7k divider)

# ---- RGB LED sinks (use SB_RGBA_DRV) ----
set_io led_r        39
set_io led_g        40
set_io led_b        41
